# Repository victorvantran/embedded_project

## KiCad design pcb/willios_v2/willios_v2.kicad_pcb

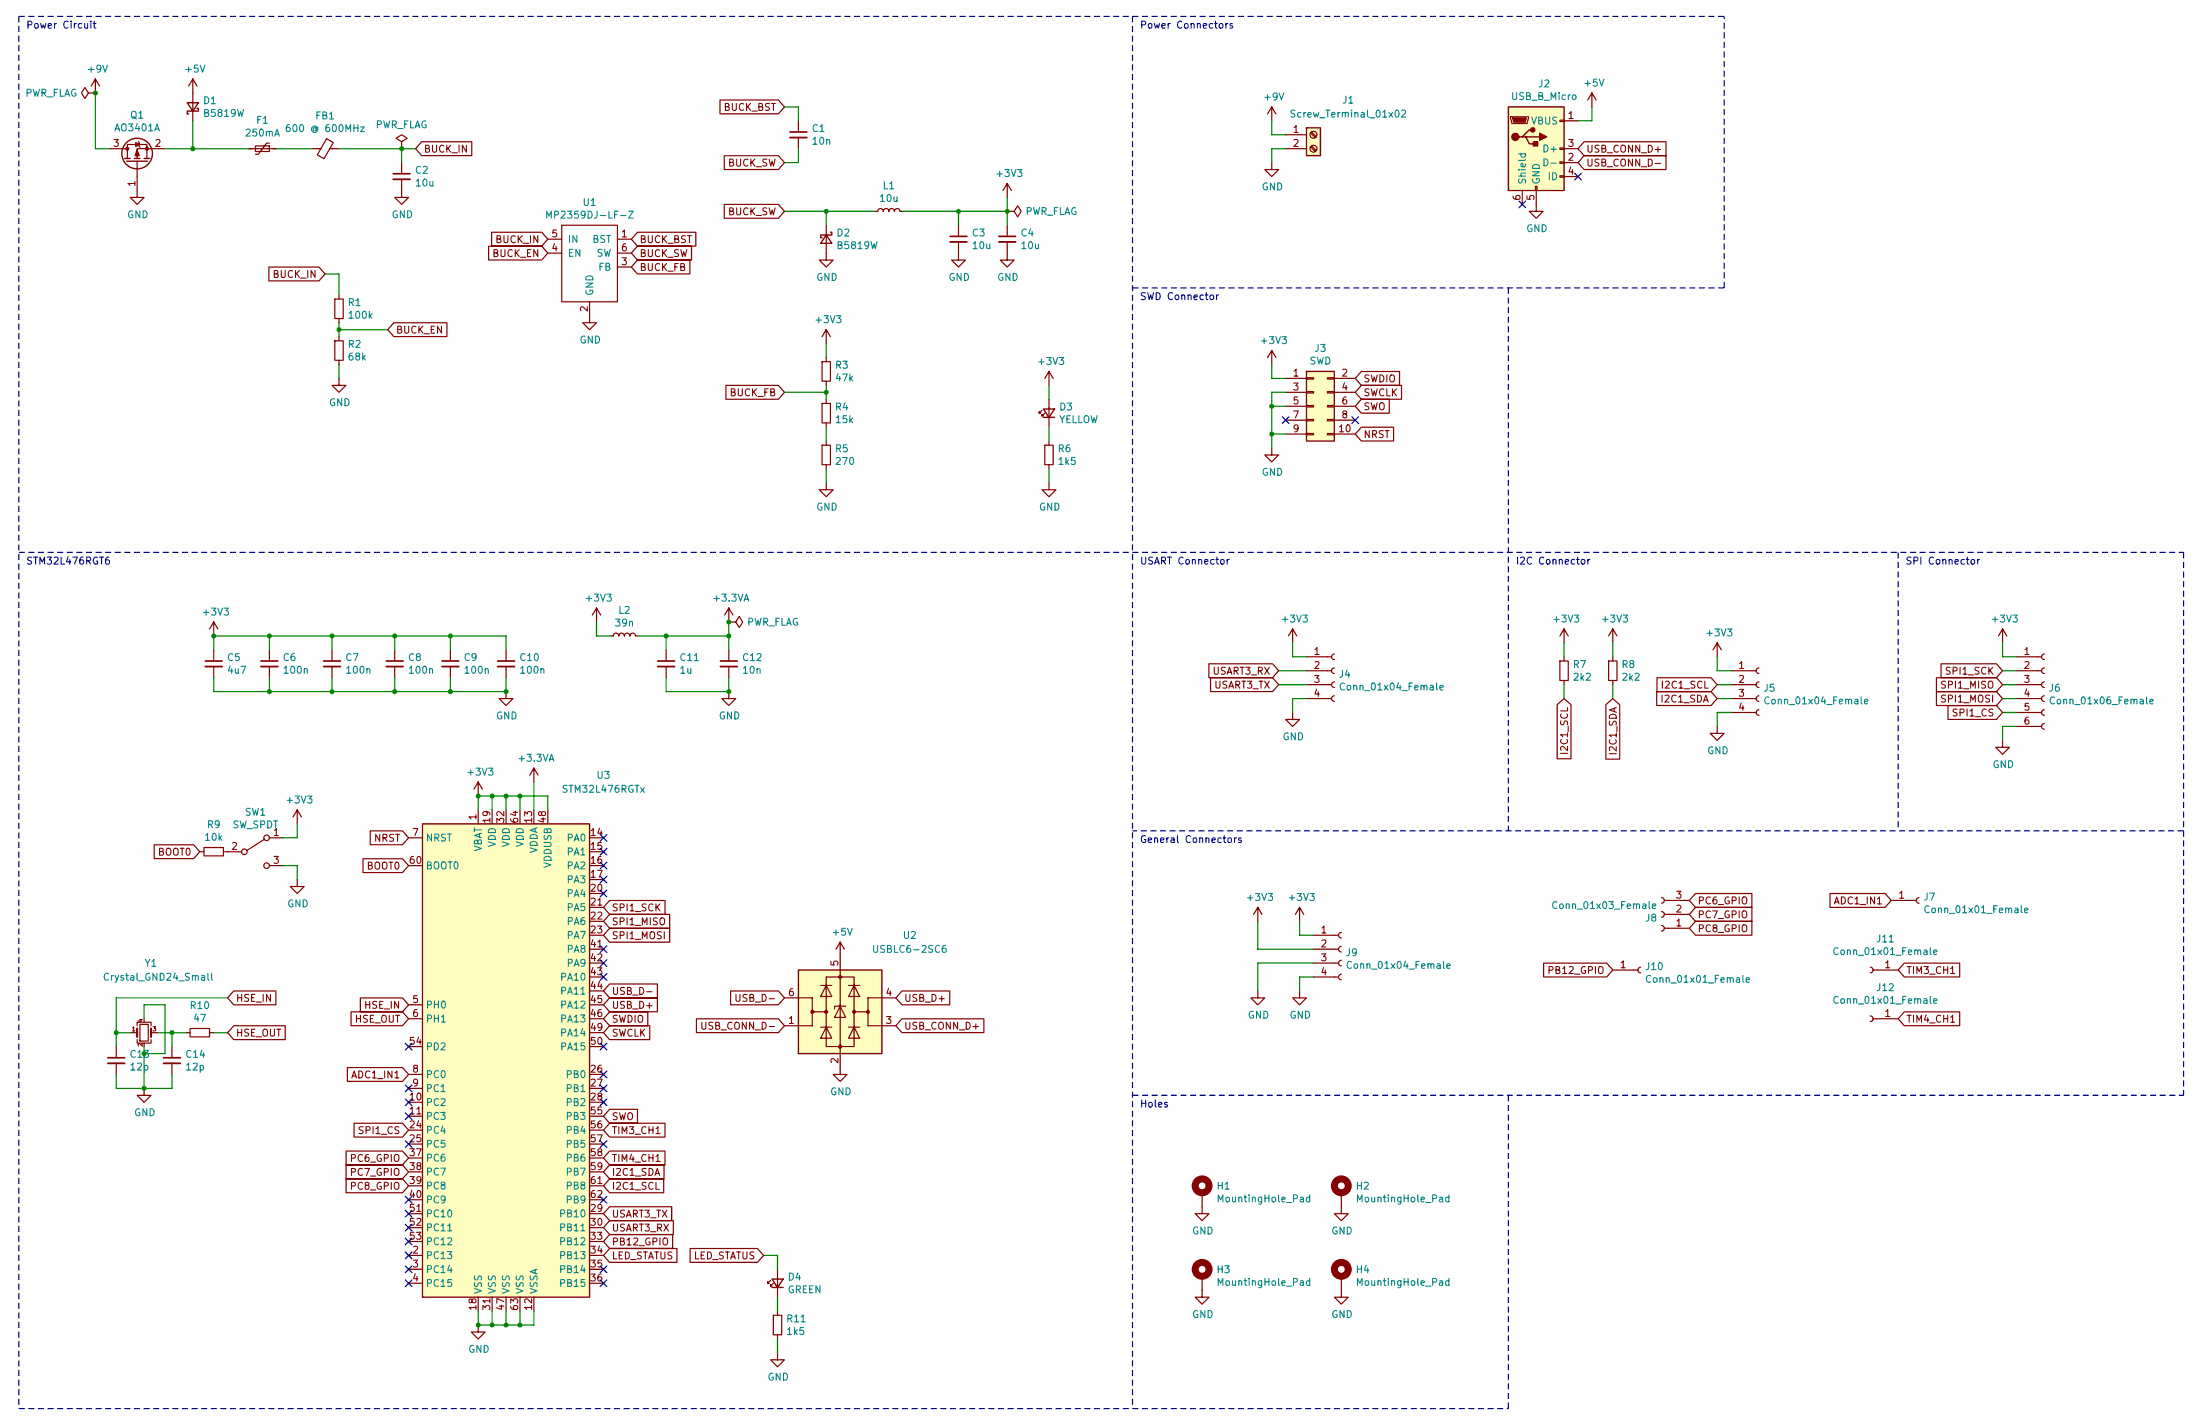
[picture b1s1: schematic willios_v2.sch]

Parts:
C1: 10n; C_0603_1608Metric
C2, C3, C4: 10u; C_1206_3216Metric
C5: 4u7; C_0603_1608Metric
C6, C7, C8, C9, C10: 100n; C_0402_1005Metric
C11: 1u; C_0402_1005Metric
C12: 10n; C_0402_1005Metric
C13, C14: 12p; C_0402_1005Metric
D1, D2: B5819W; D_SOD-123
D3: YELLOW; LED_0603_1608Metric
D4: GREEN; LED_0603_1608Metric
F1: 250mA; Fuse_1206_3216Metric
FB1: 600 @ 600MHz; L_0805_2012Metric
H1, H2, H3, H4: MountingHole_Pad; MountingHole_3.2mm_M3_Pad_Via
J1: Screw_Terminal_01x02; TerminalBlock_Phoenix_PT-1,5-2-3.5-H_1x02_P3.50mm_Horizontal
J2: USB_B_Micro; USB_Micro-B_Molex_47346-0001
J3: SWD; PinSocket_2x05_P2.54mm_Vertical
J4, J5, J9: Conn_01x04_Female; PinSocket_1x04_P2.54mm_Vertical
J6: Conn_01x06_Female; PinSocket_1x06_P2.54mm_Vertical
J7, J10, J11, J12: Conn_01x01_Female; PinSocket_1x01_P2.54mm_Vertical
J8: Conn_01x03_Female; PinSocket_1x03_P2.54mm_Vertical
L1: 10u; L_Sunlord_MWSA0518_5.4x5.2mm
L2: 39n; L_0402_1005Metric
Q1: AO3401A; SOT-23
R1: 100k; R_0603_1608Metric
R2: 68k; R_0603_1608Metric
R3: 47k; R_0603_1608Metric
R4: 15k; R_0603_1608Metric
R5: 270; R_0603_1608Metric
R6, R11: 1k5; R_0603_1608Metric
R7, R8: 2k2; R_0603_1608Metric
R9: 10k; R_0402_1005Metric
R10: 47; R_0402_1005Metric
SW1: SW_SPDT; SW_SPDT_PCM12
U1: MP2359DJ-LF-Z; SOT-23-6
U2: USBLC6-2SC6; SOT-23-6
U3: STM32L476RGTx; LQFP-64_10x10mm_P0.5mm
Y1: Crystal_GND24_Small; Crystal_SMD_3225-4Pin_3.2x2.5mm

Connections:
+3.3VA: C11.1, C12.1, L2.2, U3.13 (VDDA)
+3V3: C3.1, C4.1, C5.1, C6.1, C7.1, C8.1, C9.1, C10.1, D3.2 (A), J3.1, J4.1, J5.1, J6.1, J9.1, J9.2, L1.2, L2.1, R3.1, R7.1, R8.1, SW1.1 (A), U3.1 (VBAT), U3.19 (VDD), U3.32 (VDD), U3.48 (VDDUSB), U3.64 (VDD)
+5V: D1.2 (A), J2.1 (VBUS), U2.5 (VBUS)
+9V: J1.1, Q1.3 (D)
ADC1_IN1: J7.1, U3.8 (PC0)
BOOT0: R9.2, U3.60 (BOOT0)
BUCK_BST: C1.1, U1.1 (BST)
BUCK_EN: R1.2, R2.1, U1.4 (EN)
BUCK_FB: R3.2, R4.1, U1.3 (FB)
BUCK_IN: C2.1, FB1.1, R1.1, U1.5 (IN)
BUCK_SW: C1.2, D2.1 (K), L1.1, U1.6 (SW)
GND: C2.2, C3.2, C4.2, C5.2, C6.2, C7.2, C8.2, C9.2, C10.2, C11.2, C12.2, C13.2, C14.2, D2.2 (A), H1.1, H2.1, H3.1, H4.1, J1.2, J2.5 (GND), J3.3, J3.5, J3.9, J4.4, J5.4, J6.6, J9.3, J9.4, Q1.1 (G), R2.2, R5.2, R6.2, R11.2, SW1.3 (C), U1.2 (GND), U2.2 (GND), U3.12 (VSSA), U3.18 (VSS), U3.31 (VSS), U3.47 (VSS), U3.63 (VSS), Y1.2, Y1.4
HSE_IN: C13.1, U3.5 (PH0), Y1.1
HSE_OUT: R10.1, U3.6 (PH1)
I2C1_SCL: J5.2, R7.2, U3.61 (PB8)
I2C1_SDA: J5.3, R8.2, U3.59 (PB7)
LED_STATUS: D4.2 (A), U3.34 (PB13)
NRST: J3.10, U3.7 (NRST)
unnamed: C14.1, R10.2, Y1.3
unnamed: D1.1 (K), F1.2, Q1.2 (S)
unnamed: D3.1 (K), R6.1
unnamed: D4.1 (K), R11.1
unnamed: F1.1, FB1.2
unnamed: R4.2, R5.1
unnamed: R9.1, SW1.2 (B)
PB12_GPIO: J10.1, U3.33 (PB12)
PC6_GPIO: J8.3, U3.37 (PC6)
PC7_GPIO: J8.2, U3.38 (PC7)
PC8_GPIO: J8.1, U3.39 (PC8)
SPI1_CS: J6.5, U3.24 (PC4)
SPI1_MISO: J6.3, U3.22 (PA6)
SPI1_MOSI: J6.4, U3.23 (PA7)
SPI1_SCK: J6.2, U3.21 (PA5)
SWCLK: J3.4, U3.49 (PA14)
SWDIO: J3.2, U3.46 (PA13)
SWO: J3.6, U3.55 (PB3)
TIM3_CH1: J11.1, U3.56 (PB4)
TIM4_CH1: J12.1, U3.58 (PB6)
USART3_RX: J4.2, U3.30 (PB11)
USART3_TX: J4.3, U3.29 (PB10)
USB_CONN_D+: J2.3 (D+), U2.3 (I/O2)
USB_CONN_D-: J2.2 (D-), U2.1 (I/O1)
USB_D+: U2.4 (I/O2), U3.45 (PA12)
USB_D-: U2.6 (I/O1), U3.44 (PA11)

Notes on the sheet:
Power Circuit
Power Connectors
SWD Connector
USART Connector
I2C Connector
SPI Connector
General Connectors
STM32L476RGT6
Holes

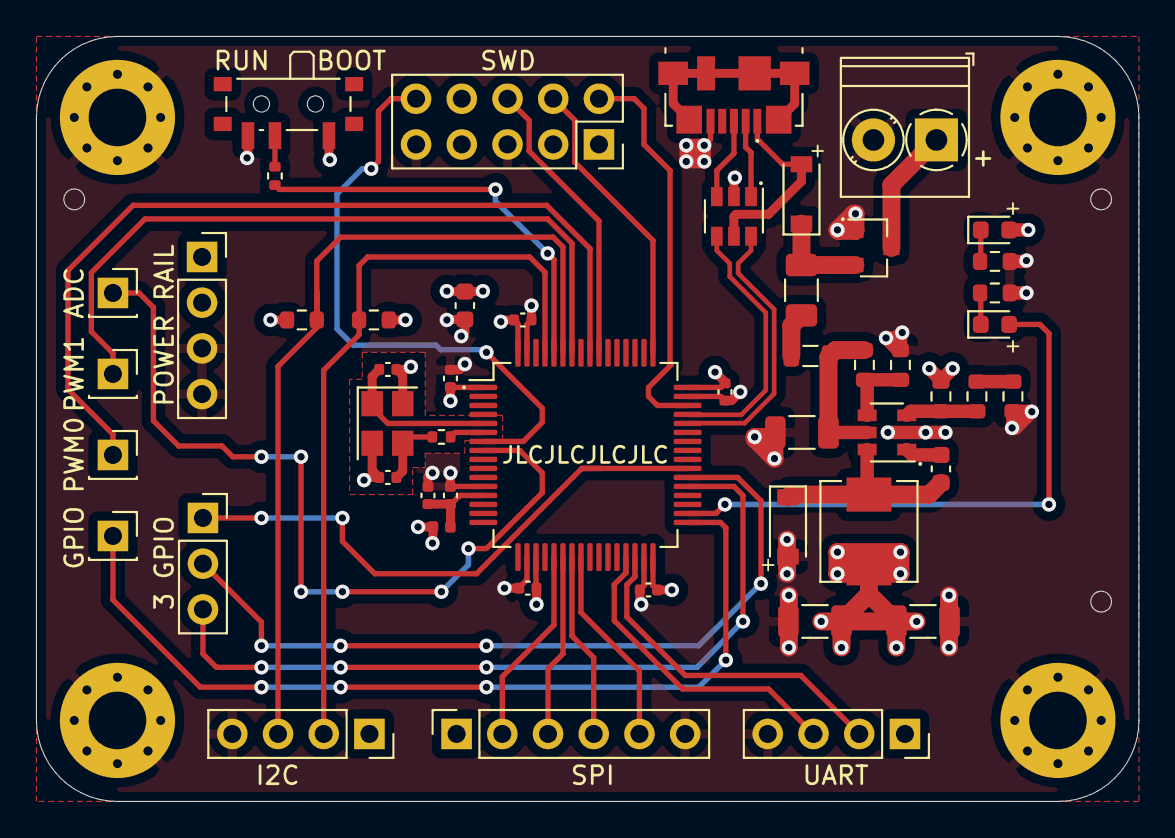
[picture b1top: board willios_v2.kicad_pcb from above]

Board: 4 copper layers, 61.2 x 42.5 mm, 55 parts (0 on the bottom side), 44 nets.

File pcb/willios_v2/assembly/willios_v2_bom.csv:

Comment,Designator,Footprint,LCSC
"10n","C1","Capacitor_SMD:C_0603_1608Metric",""
"1u","C11","Capacitor_SMD:C_0402_1005Metric",""
"10n","C12","Capacitor_SMD:C_0402_1005Metric",""
"12p","C13,C14","Capacitor_SMD:C_0402_1005Metric",""
"10u","C2,C3,C4","Capacitor_SMD:C_1206_3216Metric",""
"4u7","C5","Capacitor_SMD:C_0603_1608Metric",""
"100n","C6,C7,C8,C9,C10","Capacitor_SMD:C_0402_1005Metric",""
"B5819W","D1,D2","Diode_SMD:D_SOD-123",""
"YELLOW","D3","LED_SMD:LED_0603_1608Metric",""
"GREEN","D4","LED_SMD:LED_0603_1608Metric",""
"250mA","F1","Fuse:Fuse_1206_3216Metric",""
"600 @ 600MHz","FB1","Inductor_SMD:L_0805_2012Metric",""
"MountingHole_Pad","H1,H2,H3,H4","MountingHole:MountingHole_3.2mm_M3_Pad_Via",""
"Screw_Terminal_01x02","J1","TerminalBlock_Phoenix:TerminalBlock_Phoenix_PT-1,5-2-3.5-H_1x02_P3.50mm_Horizontal",""
"Conn_01x01_Female","J7,J10,J11,J12","Connector_PinSocket_2.54mm:PinSocket_1x01_P2.54mm_Vertical",""
"USB_B_Micro","J2","Connector_USB:USB_Micro-B_Molex_47346-0001",""
"SWD","J3","Connector_PinSocket_2.54mm:PinSocket_2x05_P2.54mm_Vertical",""
"Conn_01x04_Female","J4,J5,J9","Connector_PinSocket_2.54mm:PinSocket_1x04_P2.54mm_Vertical",""
"Conn_01x06_Female","J6","Connector_PinSocket_2.54mm:PinSocket_1x06_P2.54mm_Vertical",""
"Conn_01x03_Female","J8","Connector_PinSocket_2.54mm:PinSocket_1x03_P2.54mm_Vertical",""
"10u","L1","Inductor_SMD:L_Sunlord_MWSA0518_5.4x5.2mm",""
"39n","L2","Inductor_SMD:L_0402_1005Metric",""
"AO3401A","Q1","Package_TO_SOT_SMD:SOT-23",""
"100k","R1","Resistor_SMD:R_0603_1608Metric",""
"47","R10","Resistor_SMD:R_0402_1005Metric",""
"1k5","R6,R11","Resistor_SMD:R_0603_1608Metric",""
"68k","R2","Resistor_SMD:R_0603_1608Metric",""
"47k","R3","Resistor_SMD:R_0603_1608Metric",""
"15k","R4","Resistor_SMD:R_0603_1608Metric",""
"270","R5","Resistor_SMD:R_0603_1608Metric",""
"2k2","R7,R8","Resistor_SMD:R_0603_1608Metric",""
"10k","R9","Resistor_SMD:R_0402_1005Metric",""
"SW_SPDT","SW1","Button_Switch_SMD:SW_SPDT_PCM12",""
"MP2359DJ-LF-Z","U1","Package_TO_SOT_SMD:SOT-23-6",""
"USBLC6-2SC6","U2","Package_TO_SOT_SMD:SOT-23-6",""
"STM32L476RGTx","U3","Package_QFP:LQFP-64_10x10mm_P0.5mm",""
"Crystal_GND24_Small","Y1","Crystal:Crystal_SMD_3225-4Pin_3.2x2.5mm",""

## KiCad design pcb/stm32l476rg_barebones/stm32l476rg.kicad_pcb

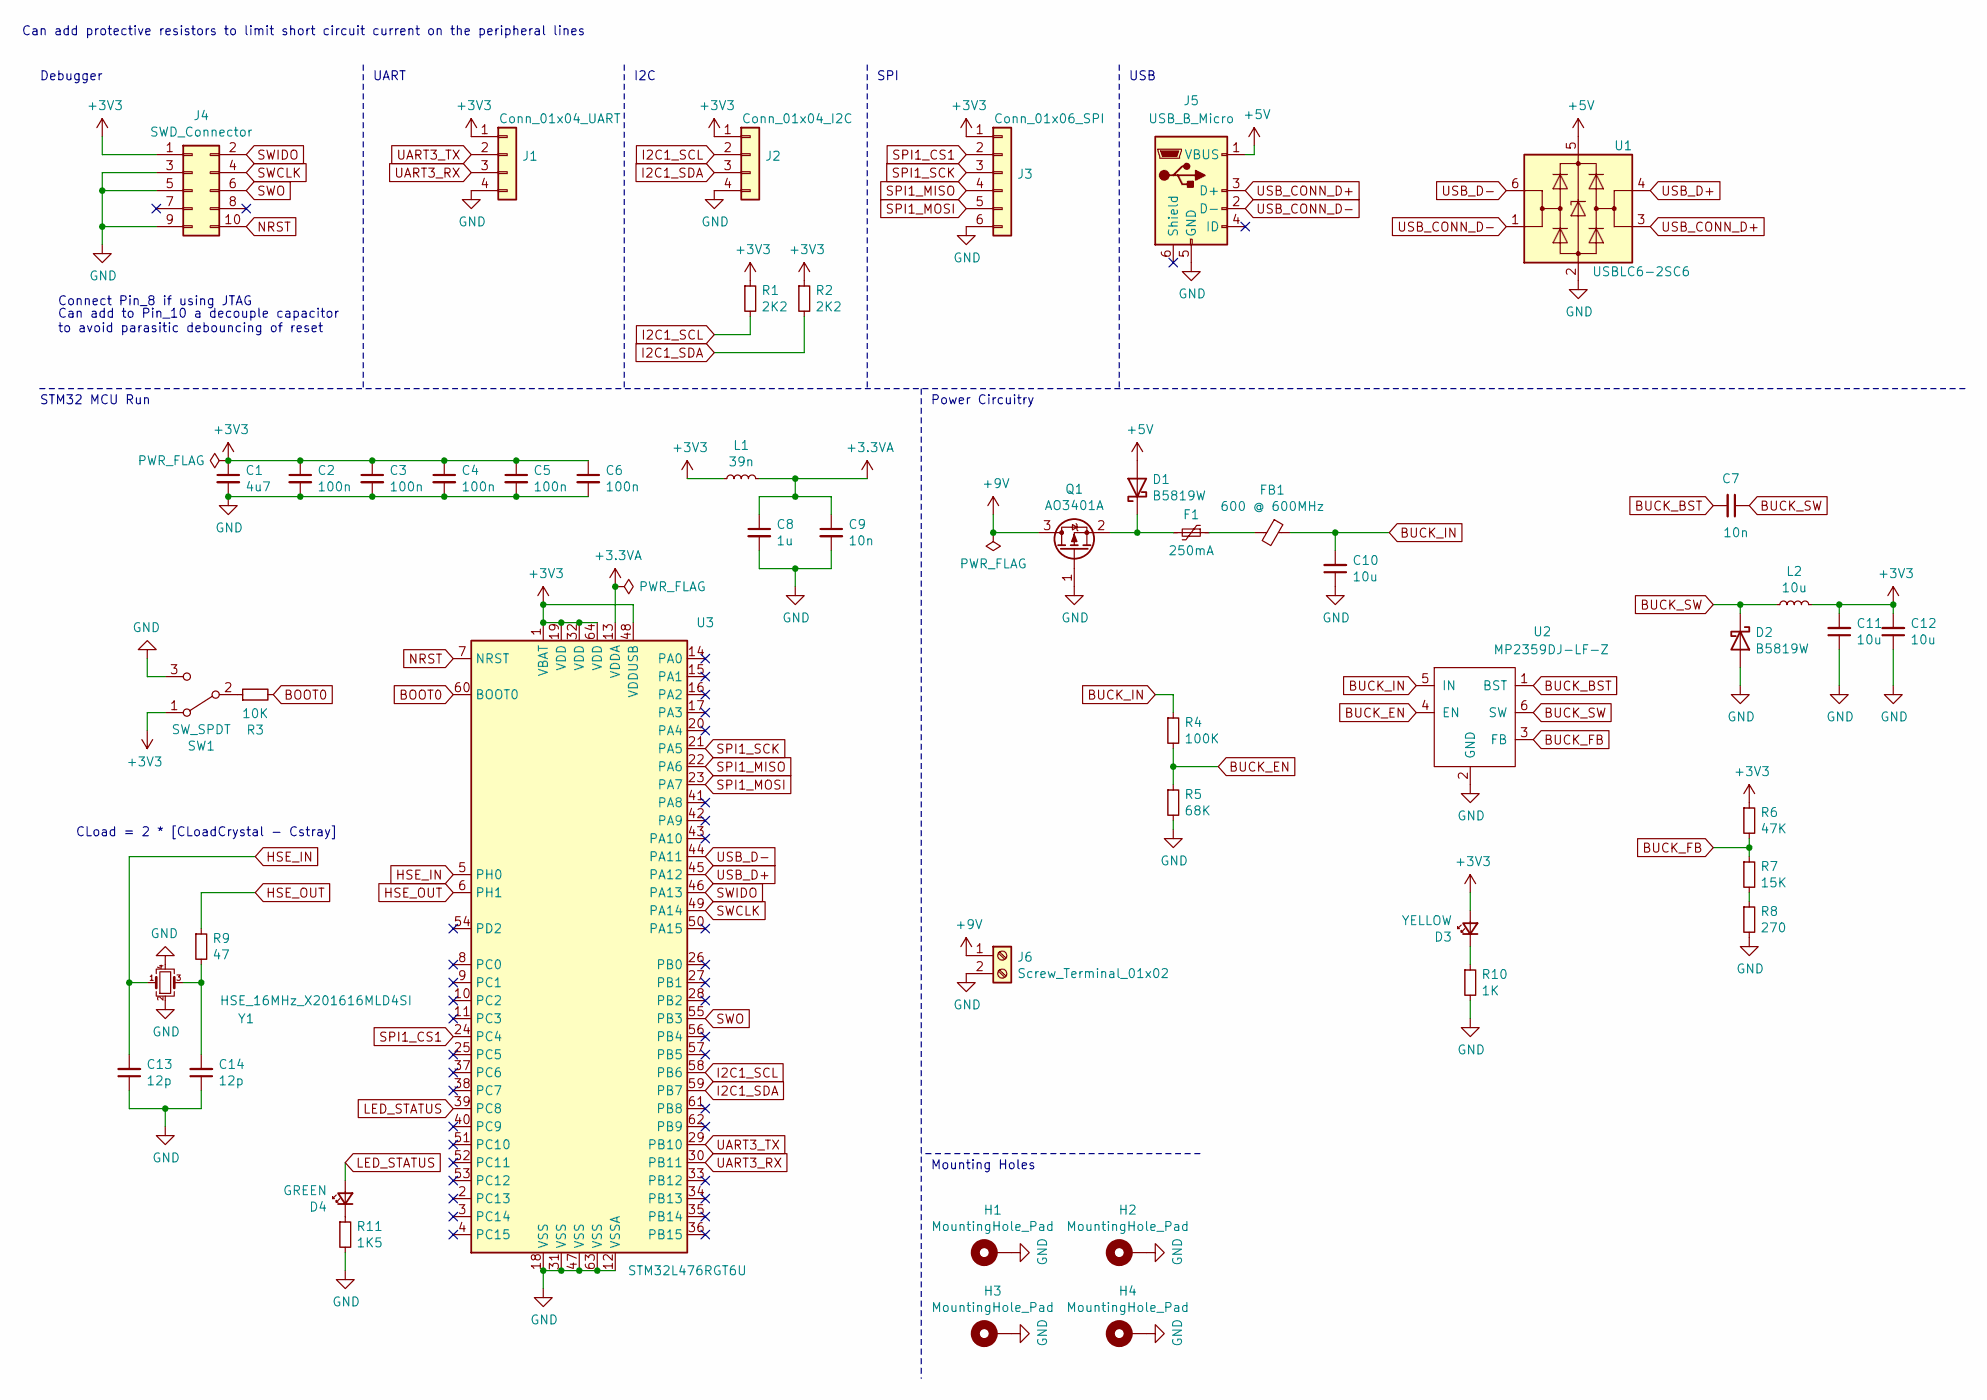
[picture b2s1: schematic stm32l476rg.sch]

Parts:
C1: 4u7; C_0603_1608Metric; LCSC Part # C19666
C2, C3, C4, C5, C6: 100n; C_0402_1005Metric; LCSC Part # C1525
C7: 10n; C_0603_1608Metric; LCSC Part # C57112
C8: 1u; C_0402_1005Metric; LCSC Part # C52923
C9: 10n; C_0402_1005Metric; LCSC Part # C15195
C10, C11, C12: 10u; C_1206_3216Metric; LCSC Part # C13585
C13, C14: 12p; C_0402_1005Metric; LCSC Part # C1547
D1, D2: B5819W; D_SOD-123; LCSC Part # C8598
D3: YELLOW; LED_0603_1608Metric; LCSC Part # C72038
D4: GREEN; LED_0603_1608Metric; LCSC Part # C72043
F1: 250mA; Fuse_1206_3216Metric; LCSC Part # C369159
FB1: 600 @ 600MHz; L_0805_2012Metric; LCSC Part # C1017
H1, H2, H3, H4: MountingHole_Pad; MountingHole_3.2mm_M3_Pad_Via
J1: Conn_01x04_UART; Molex_PicoBlade_53048-0410_1x04_P1.25mm_Horizontal
J2: Conn_01x04_I2C; Molex_PicoBlade_53048-0410_1x04_P1.25mm_Horizontal
J3: Conn_01x06_SPI; Molex_PicoBlade_53048-0610_1x06_P1.25mm_Horizontal
J4: SWD_Connector; PinHeader_2x05_P1.27mm_Vertical_SMD
J5: USB_B_Micro; USB_Micro-B_Amphenol_10103594-0001LF_Horizontal
J6: Screw_Terminal_01x02; TerminalBlock_Phoenix_PT-1,5-2-3.5-H_1x02_P3.50mm_Horizontal
L1: 39n; L_0402_1005Metric; LCSC Part # C26443
L2: 10u; L_Sunlord_MWSA0518_5.4x5.2mm; LCSC Part # C139506
Q1: AO3401A; SOT-23
R1, R2: 2K2; R_0603_1608Metric
R3: 10K; R_0402_1005Metric
R4: 100K; R_0603_1608Metric
R5: 68K; R_0603_1608Metric
R6: 47K; R_0603_1608Metric
R7: 15K; R_0603_1608Metric
R8: 270; R_0603_1608Metric
R9: 47; R_0402_1005Metric
R10: 1K; R_0603_1608Metric
R11: 1K5; R_0603_1608Metric
SW1: SW_SPDT; SW_SPDT_PCM12
U1: USBLC6-2SC6; SOT-23-6
U2: MP2359DJ-LF-Z; SOT-23-6
U3: STM32L476RGT6U; LQFP-64_10x10mm_P0.5mm
Y1: HSE_16MHz_X201616MLD4SI; Crystal_SMD_2016-4Pin_2.0x1.6mm

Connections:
+3.3VA: C8.1, C9.1, L1.2, U3.13 (VDDA)
+3V3: C1.1, C2.1, C3.1, C4.1, C5.1, C6.1, C11.2, C12.2, D3.2 (A), J1.1, J2.1, J3.1, J4.1, L1.1, L2.2, R1.1, R2.1, R6.1, SW1.1 (A), U3.1 (VBAT), U3.19 (VDD), U3.32 (VDD), U3.48 (VDDUSB), U3.64 (VDD)
+5V: D1.2 (A), J5.1 (VBUS), U1.5 (VBUS)
+9V: J6.1, Q1.3 (D)
BOOT0: R3.2, U3.60 (BOOT0)
BUCK_BST: C7.2, U2.1 (BST)
BUCK_EN: R4.2, R5.1, U2.4 (EN)
BUCK_FB: R6.2, R7.1, U2.3 (FB)
BUCK_IN: C10.2, FB1.1, R4.1, U2.5 (IN)
BUCK_SW: C7.1, D2.1 (K), L2.1, U2.6 (SW)
GND: C1.2, C2.2, C3.2, C4.2, C5.2, C6.2, C8.2, C9.2, C10.1, C11.1, C12.1, C13.1, C14.1, D2.2 (A), H1.1, H2.1, H3.1, H4.1, J1.4, J2.4, J3.6, J4.3, J4.5, J4.9, J5.5 (GND), J6.2, Q1.1 (G), R5.2, R8.2, R10.2, R11.2, SW1.3 (C), U1.2 (GND), U2.2 (GND), U3.12 (VSSA), U3.18 (VSS), U3.31 (VSS), U3.47 (VSS), U3.63 (VSS), Y1.2, Y1.4
HSE_IN: C13.2, U3.5 (PH0), Y1.1
HSE_OUT: R9.1, U3.6 (PH1)
I2C1_SCL: J2.2, R1.2, U3.58 (PB6)
I2C1_SDA: J2.3, R2.2, U3.59 (PB7)
LED_STATUS: D4.2 (A), U3.39 (PC8)
NRST: J4.10, U3.7 (NRST)
unnamed: C14.2, R9.2, Y1.3
unnamed: D1.1 (K), F1.2, Q1.2 (S)
unnamed: D3.1 (K), R10.1
unnamed: D4.1 (K), R11.1
unnamed: F1.1, FB1.2
unnamed: R3.1, SW1.2 (B)
unnamed: R7.2, R8.1
SPI1_CS1: J3.2, U3.24 (PC4)
SPI1_MISO: J3.4, U3.22 (PA6)
SPI1_MOSI: J3.5, U3.23 (PA7)
SPI1_SCK: J3.3, U3.21 (PA5)
SWCLK: J4.4, U3.49 (PA14)
SWIDO: J4.2, U3.46 (PA13)
SWO: J4.6, U3.55 (PB3)
UART3_RX: J1.3, U3.30 (PB11)
UART3_TX: J1.2, U3.29 (PB10)
USB_CONN_D+: J5.3 (D+), U1.3 (I/O2)
USB_CONN_D-: J5.2 (D-), U1.1 (I/O1)
USB_D+: U1.4 (I/O2), U3.45 (PA12)
USB_D-: U1.6 (I/O1), U3.44 (PA11)

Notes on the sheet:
STM32 MCU Run
CLoad = 2 * [CLoadCrystal - Cstray]
Power Circuitry
Connect Pin_8 if using JTAG
Can add to Pin_10 a decouple capacitor to avoid parasitic debouncing of reset
Debugger
I2C
Can add protective resistors to limit short circuit current on the peripheral lines
USB
SPI
UART
Mounting Holes

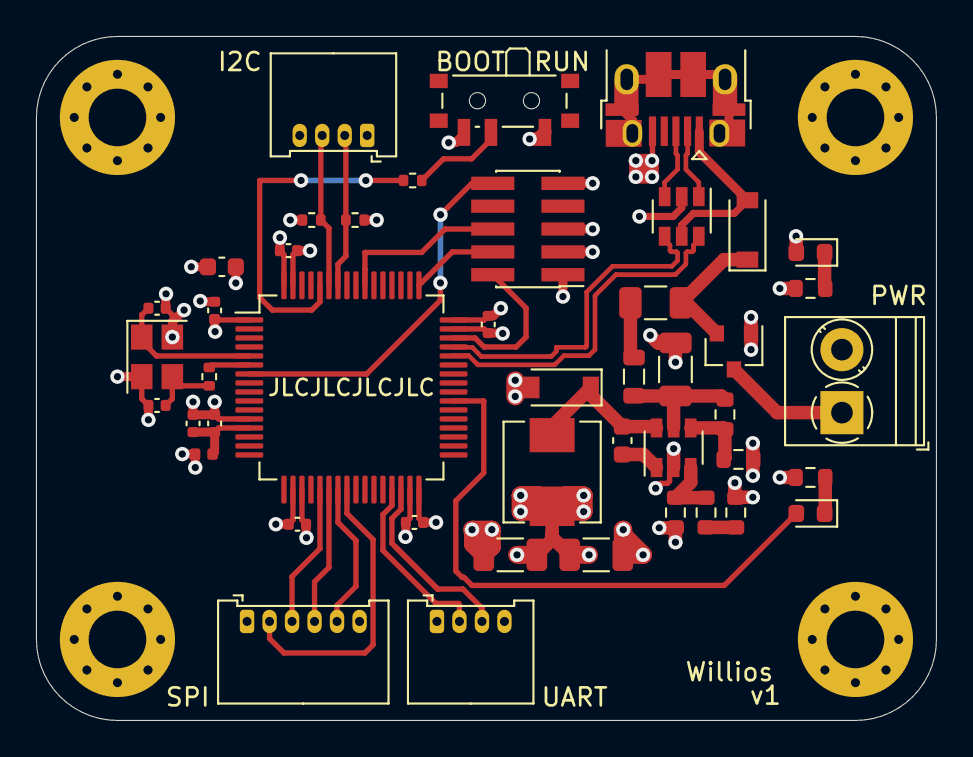
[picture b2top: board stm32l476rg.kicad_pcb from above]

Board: 4 copper layers, 50.0 x 38.0 mm, 49 parts (0 on the bottom side), 37 nets.

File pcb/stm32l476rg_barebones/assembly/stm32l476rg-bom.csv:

Comment,Designator,Footprint,LCSC
"4u7","C1","Capacitor_SMD:C_0603_1608Metric",""
"10u","C10,C11,C12","Capacitor_SMD:C_1206_3216Metric",""
"12p","C13,C14","Capacitor_SMD:C_0402_1005Metric",""
"100n","C2,C3,C4,C5,C6","Capacitor_SMD:C_0402_1005Metric",""
"10n","C7","Capacitor_SMD:C_0603_1608Metric",""
"1u","C8","Capacitor_SMD:C_0402_1005Metric",""
"10n","C9","Capacitor_SMD:C_0402_1005Metric",""
"B5819W","D1,D2","Diode_SMD:D_SOD-123",""
"YELLOW","D3","LED_SMD:LED_0603_1608Metric",""
"GREEN","D4","LED_SMD:LED_0603_1608Metric",""
"250mA","F1","Fuse:Fuse_1206_3216Metric",""
"600 @ 600MHz","FB1","Inductor_SMD:L_0805_2012Metric",""
"MountingHole_Pad","H1,H2,H3,H4","MountingHole:MountingHole_3.2mm_M3_Pad_Via",""
"Conn_01x04_UART","J1","Connector_Molex:Molex_PicoBlade_53048-0410_1x04_P1.25mm_Horizontal",""
"Conn_01x04_I2C","J2","Connector_Molex:Molex_PicoBlade_53048-0410_1x04_P1.25mm_Horizontal",""
"Conn_01x06_SPI","J3","Connector_Molex:Molex_PicoBlade_53048-0610_1x06_P1.25mm_Horizontal",""
"SWD_Connector","J4","Connector_PinHeader_1.27mm:PinHeader_2x05_P1.27mm_Vertical_SMD",""
"USB_B_Micro","J5","Connector_USB:USB_Micro-B_Amphenol_10103594-0001LF_Horizontal",""
"Screw_Terminal_01x02","J6","TerminalBlock_Phoenix:TerminalBlock_Phoenix_PT-1,5-2-3.5-H_1x02_P3.50mm_Horizontal",""
"39n","L1","Inductor_SMD:L_0402_1005Metric",""
"10u","L2","Inductor_SMD:L_Sunlord_MWSA0518_5.4x5.2mm",""
"AO3401A","Q1","Package_TO_SOT_SMD:SOT-23",""
"2K2","R1,R2","Resistor_SMD:R_0402_1005Metric",""
"1K","R10","Resistor_SMD:R_0603_1608Metric",""
"1K5","R11","Resistor_SMD:R_0603_1608Metric",""
"10K","R3","Resistor_SMD:R_0402_1005Metric",""
"100K","R4","Resistor_SMD:R_0603_1608Metric",""
"68K","R5","Resistor_SMD:R_0603_1608Metric",""
"47K","R6","Resistor_SMD:R_0603_1608Metric",""
"15K","R7","Resistor_SMD:R_0603_1608Metric",""
"270","R8","Resistor_SMD:R_0603_1608Metric",""
"47","R9","Resistor_SMD:R_0402_1005Metric",""
"SW_SPDT","SW1","Button_Switch_SMD:SW_SPDT_PCM12",""
"USBLC6-2SC6","U1","Package_TO_SOT_SMD:SOT-23-6",""
"MP2359DJ-LF-Z","U2","Package_TO_SOT_SMD:SOT-23-6",""
"STM32L476RGT6U","U3","Package_QFP:LQFP-64_10x10mm_P0.5mm",""
"HSE_16MHz","Y1","Crystal:Crystal_SMD_3225-4Pin_3.2x2.5mm",""

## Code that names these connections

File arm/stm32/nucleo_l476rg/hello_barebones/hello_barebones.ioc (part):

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PA6.Mode=Full_Duplex_Master
Mcu.UserName=STM32L476RGTx
PB10.Mode=Asynchronous
PH0-OSC_IN\ (PH0).Signal=RCC_OSC_IN
PA11.Mode=Device_Only
PB11.Signal=USART3_RX
PB13.Signal=GPIO_Output
RCC.SYSCLKSource=RCC_SYSCLKSOURCE_PLLCLK
PB3\ (JTDO-TRACESWO).Signal=SYS_JTDO-SWO
PA14\ (JTCK-SWCLK).Signal=SYS_JTCK-SWCLK
PA12.Signal=USB_OTG_FS_DP
PA14\ (JTCK-SWCLK).GPIOParameters=GPIO_Label
PB6.Signal=S_TIM4_CH1
PC7.Signal=GPIO_Output
PH1-OSC_OUT\ (PH1).Mode=HSE-External-Oscillator
RCC.HSE_VALUE=16000000
PB7.Signal=I2C1_SDA
Mcu.Package=LQFP64
PA6.Signal=SPI1_MISO
PA13\ (JTMS-SWDIO).Signal=SYS_JTMS-SWDIO
PA13\ (JTMS-SWDIO).GPIOParameters=GPIO_Label
PH0-OSC_IN\ (PH0).Mode=HSE-External-Oscillator
PA5.Mode=Full_Duplex_Master
PA14\ (JTCK-SWCLK).Mode=Trace_Asynchronous_SW
PA7.Mode=Full_Duplex_Master
PC8.Signal=GPIO_Output
PC4.Signal=GPIO_Output
PC6.Signal=GPIO_Output
PC15-OSC32_OUT\ (PC15).Signal=RCC_OSC32_OUT
PA14\ (JTCK-SWCLK).GPIO_Label=TCK
PB3\ (JTDO-TRACESWO).GPIO_Label=SWO
PC0.Signal=ADCx_IN1
boardIOC=true
PH1-OSC_OUT\ (PH1).Signal=RCC_OSC_OUT
PB11.Mode=Asynchronous
PB10.Signal=USART3_TX
PA5.Signal=SPI1_SCK
board=NUCLEO-L476RG
PB3\ (JTDO-TRACESWO).GPIOParameters=GPIO_Label
PA13\ (JTMS-SWDIO).GPIO_Label=TMS
PB3\ (JTDO-TRACESWO).Mode=Trace_Asynchronous_SW
Mcu.Name=STM32L476R(C-E-G)Tx
PA13\ (JTMS-SWDIO).Mode=Trace_Asynchronous_SW
RCC.SYSCLKFreq_VALUE=80000000
PA12.Mode=Device_Only
PC14-OSC32_IN\ (PC14).Signal=RCC_OSC32_IN
PB7.Mode=I2C
PA11.Signal=USB_OTG_FS_DM
PB8.Mode=I2C
PB8.Signal=I2C1_SCL
PB12.Signal=GPIO_Output
PA7.Signal=SPI1_MOSI
PB4\ (NJTRST).Signal=S_TIM3_CH1

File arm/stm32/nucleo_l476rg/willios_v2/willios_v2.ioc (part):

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Mcu.UserName=STM32L476RGTx
PB10.Mode=Asynchronous
PH0-OSC_IN\ (PH0).Signal=RCC_OSC_IN
PB11.Signal=USART3_RX
PB13.Signal=GPIO_Output
RCC.SYSCLKSource=RCC_SYSCLKSOURCE_PLLCLK
PA14\ (JTCK-SWCLK).Signal=SYS_JTCK-SWCLK
PA14\ (JTCK-SWCLK).GPIOParameters=GPIO_Label
PB6.Signal=S_TIM4_CH1
PC7.Signal=GPIO_Output
PH1-OSC_OUT\ (PH1).Mode=HSE-External-Oscillator
RCC.HSE_VALUE=16000000
Mcu.Package=LQFP64
PA13\ (JTMS-SWDIO).Signal=SYS_JTMS-SWDIO
PA13\ (JTMS-SWDIO).GPIOParameters=GPIO_Label
PH0-OSC_IN\ (PH0).Mode=HSE-External-Oscillator
PA14\ (JTCK-SWCLK).Mode=Serial_Wire
PC8.Signal=GPIO_Output
PC6.Signal=GPIO_Output
PA14\ (JTCK-SWCLK).GPIO_Label=TCK
boardIOC=true
PH1-OSC_OUT\ (PH1).Signal=RCC_OSC_OUT
PB11.Mode=Asynchronous
PB10.Signal=USART3_TX
board=NUCLEO-L476RG
PA13\ (JTMS-SWDIO).GPIO_Label=TMS
Mcu.Name=STM32L476R(C-E-G)Tx
PA13\ (JTMS-SWDIO).Mode=Serial_Wire
RCC.SYSCLKFreq_VALUE=80000000
PB4\ (NJTRST).Signal=S_TIM3_CH1

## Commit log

2021-04-02 Removed extraneous project
2021-04-04 Test full duplex communication
2021-04-07 Added ultrasonic sensor
2021-04-09 Added UART echo
2021-04-09 Updated terminology for dataframe
2021-04-12 Replaced LCD with USB to TTL serial UART communication
2021-04-14 Established echo for cstring
2021-04-14 Established ADC
2021-04-14 Added adc_complete interrupt
2021-04-15 Added timer blink
2021-04-16 Added timer interrupt and input capture mode tests
2021-04-16 Established input compare match interrupt width and output compare match
2021-04-17 Added pulse width modulation for varying LED brightness and stepper motor control
2021-04-24 old version
2021-04-26 Added stm32 tinker
2021-04-28 Added sample esp32 on vsc using platformio to build, flash, and monitor
2021-04-28 Added esp32 tinker
2021-05-04 Tinkered ultrasonic sensor and servo motor on the nucleo_l476rg
2021-05-09 Established ultrasonic sensor and servo for pid ball balance
2021-05-09 Tinker semaphore
2021-05-10 Tinker event groups/flags
2021-05-10 Replaced ultrasonic sensor task with pwm trigger channels
2021-05-10 Added proprtional path
2021-05-12 Tinker derivative path
2021-05-13 Added average filter for ultrasonic sensors
2021-05-15 Demo i2c using a driver library for bme280
2021-05-18 Added hello_adc intro
2021-05-22 Implementing UART ring buffer
2021-05-22 Implementing UART ring buffer part 2
2021-05-22 Implementing UART ring buffer part 3, compile fix
2021-05-22 Established UART Ring Buffer
2021-05-23 Established uart ring buffer general
2021-05-24 Established variable UART
2021-05-24 Established variable UART structured
2021-05-24 Pre-UART parsing
2021-05-24 Accounting parsing UART for rollover
2021-05-24 Fixed wrap-around UART DMA parse
2021-05-28 Cleaning UART DMA IDLE Command
2021-05-29 Send and receive uart command dma idle
2021-05-29 putty implicit CR idle delay bug found
2021-05-29 Fixed unroll wrap-around issue
2021-05-29 Established reset on rx buffer overflow
2021-05-30 Differentiated between pointer to string literal and char array
2021-05-30 Established DMA transmit
2021-05-30 Established hello_thingspeak
2021-05-30 Cleaned ThingSpeak driver
2021-05-30 Cleaned ThingSpeak driver 2
2021-05-31 Successfully communicated with ESP8266 with AT command
2021-05-31 WOrking for CRLF ending for AT commands and messages
2021-05-31 Successfully sent data to thingspeak
2021-06-02 Established task notification
2021-06-02 Transmit ThingSpeak data event
2021-06-02 Adjusted task size
2021-06-02 Adjusted string compare with strnstr
2021-06-05 Established BME280 driver
2021-06-05 Got BME280 calibrated temperature reading
2021-06-05 Got BME280 calibrated pressure reading
2021-06-05 Got BME280 calibrated humidity reading
2021-06-06 Read SPI Chip ID
2021-06-07 BME280 SPI configurations
2021-06-07 Established BME280 SPI init*
2021-06-07 Renamed I2C functions
2021-06-08 Established SPI BME280
2021-06-08 Added BME280 comments
2021-06-08 Used eziya microsd adapter library
2021-06-08 Reading piece from microSD
2021-06-09 Established piece composition and command
2021-06-09 Mapped G string
2021-06-09 Mapped string notes of d,a,e
2021-06-09 Established composition state machine
2021-06-14 Established pitch orientation
2021-06-15 Established lights and ADC interrupt for pitch correction
2021-06-15 Established play tick and goal
2021-06-22 Established barebones chip
2021-06-23 Adding peripherals to barebones
2021-06-23 Established pcb for barebones
2021-06-23 Schematic layout done
2021-06-23 Added SPI to barebomes
2021-06-24 Layed out barebones board
2021-06-24 Pre barebones route
2021-06-24 Traced barebones
2021-06-24 Barebones connector fix
2021-06-24 Changed pull up resistor size for i2c to get basic part
2021-06-24 Resized crystal oscillator
2021-06-24 Exported files for manufacturing
2021-06-25 Curated bill list
2021-07-09 Established willios_v2 (2.54mm pinout)
2021-07-09 Added more testings for barebones board
2021-07-09 Established schematic willios_v2
2021-07-09 Layout willios_v2
2021-07-09 Established layout and cut
2021-07-10 Routing pre-oscillator
2021-07-10 Completed layout willios v2
2021-07-10 Created BOM file
2021-07-10 Ordered willios_v2
2021-07-13 Prepare ui state machine
2021-07-13 Established UI c++
2021-07-14 UI OOP
2021-07-14 Separated ui states
2021-07-15 Opt for polymorphism
2021-07-15 Singleton FSM
2021-07-17 Pre test neopixel1515
2021-07-18 Testing sk6805-ec15
2021-07-20 tinkering with button
2021-07-21 Pre object-oriented
2021-07-21 Singleton menu to Object oriented
2021-07-21 Pre modes
2021-07-27 Match pc with laptop
2021-07-28 Established willios_v2 for tinkering c++
2021-07-28 WS2812B object oriented
